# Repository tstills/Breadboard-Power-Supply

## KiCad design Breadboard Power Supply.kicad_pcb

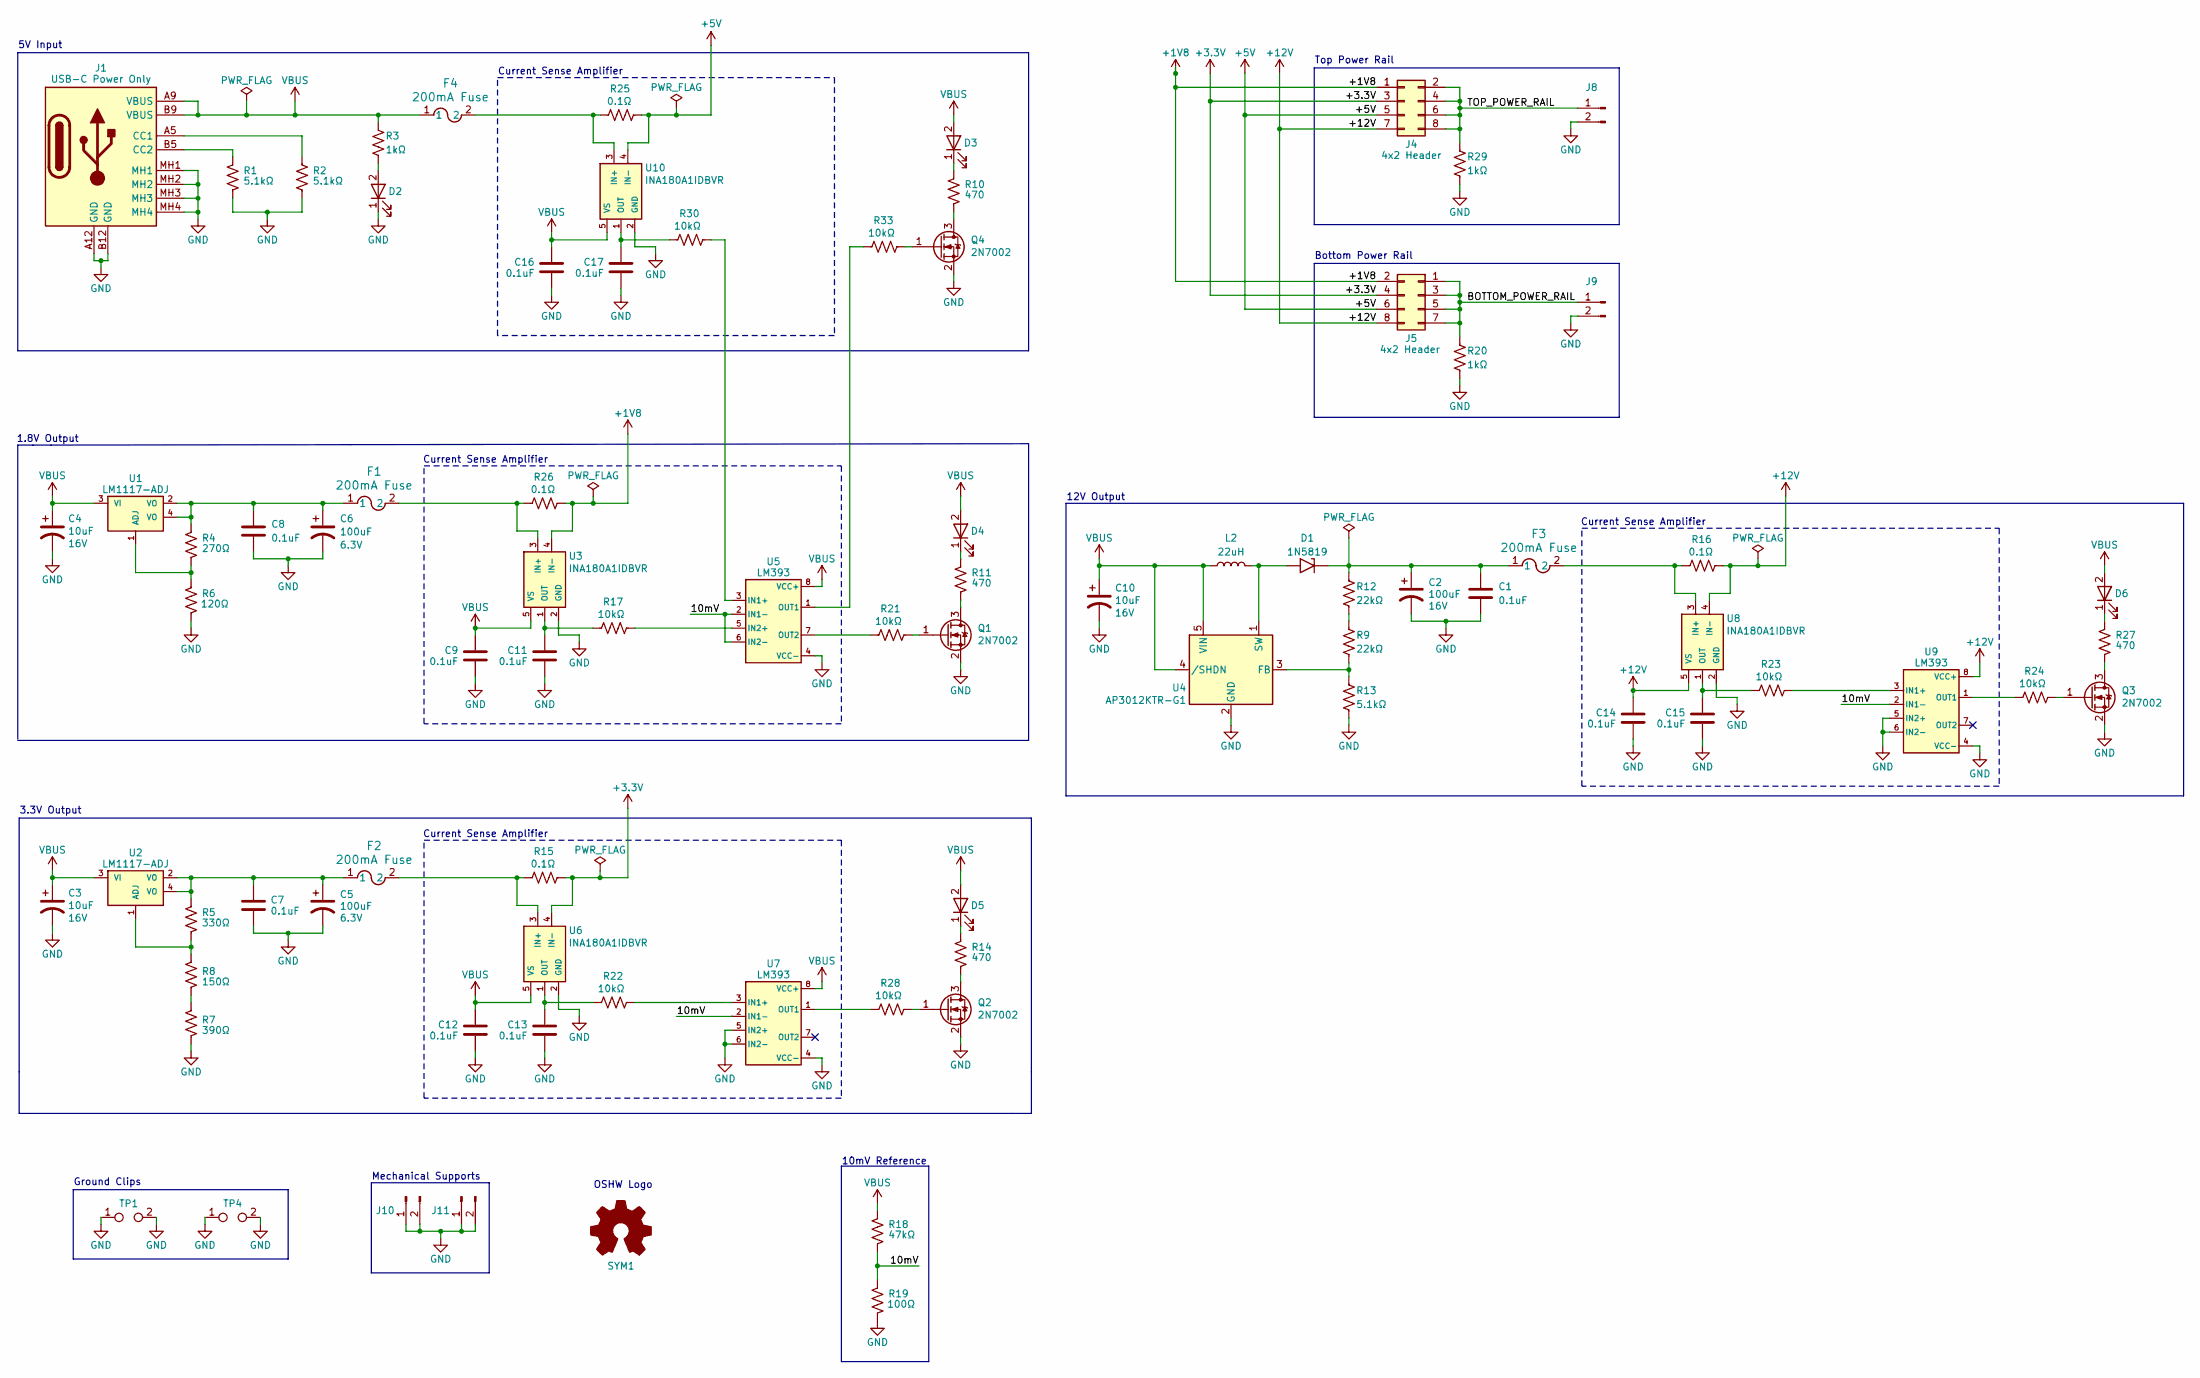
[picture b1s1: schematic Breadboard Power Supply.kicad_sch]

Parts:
C1, C7, C8, C9, C11, C12, C13, C14, C15, C16, C17: 0.1uF; C_0402_1005Metric; Digi-Key Part Num 490-14603-1-ND
C2: 100uF; 100uF 16V Capacitor; Voltage 16V; Mfg Part Num 16ZLH100MEFC5X11; Digi-Key Part Num 1189-1148-ND
C3, C4, C10: 10uF; C_0805_2012Metric; Voltage 16V; Mfg Part Num TCTP1C106M8R; Digi-Key Part Num TCTP1C106M8R
C5, C6: 100uF; 100uF 6.3V Capacitor; Voltage 6.3V; Mfg Part Num F930J107KAA; Digi-Key Part Num 478-8152-1-ND
D1: 1N5819; D_SOD-123F; Mfg Part Num 1N5819HW1-7-F; Digi-Key Part Num 1N5819HW1-7-FDICT-ND
D2, D3, D4, D5, D6: LED 0603; Mfg Part Num SML-D12U8WT86; Digi-Key Part Num 846-SML-D12U8WT86CT-ND
F1, F2, F3, F4: 200mA Fuse; Resettable Fuse 200mA; Mfg Part Num 0ZCJ0020FF2E; DigiKey Part Num 5923-0ZCJ0020FF2ECT-ND
J1: USB-C Power Only; Mfg Part Num 217175-0001; Digi-Key Part Num 900-2171750001CT-ND
J4, J5: 4x2 Header; PinHeader_2x04_P2.54mm_Vertical
J8: Conn_01x02_Male; PinHeader_1x02_P2.54mm_Vertical
J9, J10, J11: Conn_01x02_Male; PinHeader_1x02_P2.54mm_Vertical; Digi-Key Part Num 2057-PH1-02-UA-ND
L2: 22uH; L_0805_2012Metric; Mfg Part Num MLZ2012P220WT000; Digi-Key Part Num 445-15751-1-ND
Q1, Q2, Q3, Q4: 2N7002; SOT-23; Mfg Part Num 2N7002; DigiKey Part Num 4878-2N7002CT-ND
R1, R2: 5.1kΩ; R_0402_1005Metric; Digi-Key Part Num 10-ERJ-UP3F5101VCT-ND
R3, R20, R29: 1kΩ; R_0402_1005Metric; Mfg Part Num RC0603FR-07910RL; Digi-Key Part Num 311-910HRCT-ND
R4: 270Ω; R_0402_1005Metric; Digi-Key Part Num 10-ERJ-UP3F5101VCT-ND
R5: 330Ω; R_0402_1005Metric; Digi-Key Part Num 10-ERJ-UP3F5101VCT-ND
R6: 120Ω; R_0402_1005Metric; Digi-Key Part Num 10-ERJ-UP3F5101VCT-ND
R7: 390Ω; R_0402_1005Metric; Digi-Key Part Num 10-ERJ-UP3F5101VCT-ND
R8: 150Ω; R_0402_1005Metric; Digi-Key Part Num 10-ERJ-UP3F5101VCT-ND
R9, R12: 22kΩ; R_0402_1005Metric; Mfg Part Num RC0603FR-07910RL; Digi-Key Part Num 311-910HRCT-ND
R10, R11, R14, R27: 470; R_0402_1005Metric; Digi-Key Part Num 10-ERJ-UP3F5101VCT-ND
R13: 5.1kΩ; R_0402_1005Metric; Mfg Part Num RC0603FR-07910RL; Digi-Key Part Num 311-910HRCT-ND
R15, R16, R25, R26: 0.1Ω; R_0402_1005Metric; Digi-Key Part Num 10-ERJ-UP3F5101VCT-ND
R17, R21, R22, R23, R24, R28, R30, R33: 10kΩ; R_0402_1005Metric; Digi-Key Part Num 10-ERJ-UP3F5101VCT-ND
R18: 47kΩ; R_0402_1005Metric; Digi-Key Part Num 10-ERJ-UP3F5101VCT-ND
R19: 100Ω; R_0402_1005Metric; Digi-Key Part Num 10-ERJ-UP3F5101VCT-ND
SYM1: Logo_Open_Hardware_Small; OSHW-Logo_7.5x8mm_SilkScreen
TP1: TestPoint_2Pole; Keystone 1430; Digi-Key Part Num 36-1430-1-ND
TP4: TestPoint_2Pole; Keystone 1430; Digi-Key Part Num 36-1287-ND
U1: LM1117-ADJ; PARTREV O; Digi-Key Part Num 296-21114-1-ND
U2: LM1117-ADJ; Mfg Part Num TLV1117-50CDCYR; Digi-Key Part Num 296-21114-1-ND
U3, U6, U8, U10: INA180A1IDBVR; Mfg Part Num INA180A1IDBVR; Digi-Key Part Num 296-47652-1-ND
U4: AP3012KTR-G1; SOT-23-5_DIO; Mfg Part Num AP3012KTR-G1; DigiKey Part Num AP3012KTR-G1DICT-ND
U5, U7, U9: LM393; LM393 DFN8; Mfg Part Num LM393LVDSGR; Digi-Key Part Num 296-LM393LVDSGRCT-ND

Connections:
+1V8: J4.1, J5.2, R26.2, U3.4 (IN-)
+3.3V: J4.3, J5.4, R15.2, U6.4 (IN-)
+5V: J4.5, J5.6, R25.2, U10.4 (IN-)
+12V: C14.2, J4.7, J5.8, R16.2, U8.4 (IN-), U8.5 (VS), U9.8 (VCC+)
/10mV: R18.2, R19.1, U5.2 (IN1-), U5.6 (IN2-), U7.2 (IN1-), U9.2 (IN1-)
/BOTTOM_POWER_RAIL: J5.1, J5.3, J5.5, J5.7, J9.1, R20.1
/TOP_POWER_RAIL: J4.2, J4.4, J4.6, J4.8, J8.1, R29.1
GND: C1.2, C2.2, C3.2, C4.2, C5.2, C6.2, C7.2, C8.2, C9.1, C10.2, C11.1, C12.1, C13.1, C14.1, C15.1, C16.1, C17.1, D2.1, J1.A12 (GND), J1.B12 (GND), J1.MH1, J1.MH2, J1.MH3, J1.MH4, J8.2, J9.2, J10.1, J10.2, J11.1, J11.2, Q1.2 (S), Q2.2 (S), Q3.2 (S), Q4.2 (S), R1.2, R2.2, R6.2, R7.2, R13.2, R19.2, R20.2, R29.2, TP1.1, TP1.2, TP4.1, TP4.2, U3.2 (GND), U4.2 (GND), U5.4 (VCC-), U6.2 (GND), U7.4 (VCC-), U7.5 (IN2+), U7.6 (IN2-), U8.2 (GND), U9.4 (VCC-), U9.5 (IN2+), U9.6 (IN2-), U10.2 (GND)
unnamed: C5.1, C7.1, F2.1, R5.1, U2.2 (VO), U2.4 (VO)
unnamed: C6.1, C8.1, F1.1, R4.1, U1.2 (VO), U1.4 (VO)
unnamed: C1.1, C2.1, D1.1 (A1), F3.1, R12.1
unnamed: D1.2 (A2), L2.2, U4.1 (SW)
unnamed: D2.2, R3.2
unnamed: D3.1, R10.1
unnamed: D4.1, R11.1
unnamed: D5.1, R14.1
unnamed: D6.1, R27.1
unnamed: J1.A5 (CC1), R2.1
unnamed: J1.B5 (CC2), R1.1
unnamed: Q1.3 (D), R11.2
unnamed: Q1.1 (G), R21.2
unnamed: Q2.3 (D), R14.2
unnamed: Q2.1 (G), R28.2
unnamed: Q3.3 (D), R27.2
unnamed: Q3.1 (G), R24.2
unnamed: Q4.3 (D), R10.2
unnamed: Q4.1 (G), R33.2
unnamed: R7.1, R8.2
unnamed: R9.1, R12.2
unnamed: R4.2, R6.1, U1.1 (ADJ)
unnamed: R5.2, R8.1, U2.1 (ADJ)
unnamed: F1.2, R26.1, U3.3 (IN+)
unnamed: C11.2, R17.1, U3.1 (OUT)
unnamed: R9.2, R13.1, U4.3 (FB)
unnamed: R30.2, U5.3 (IN1+)
unnamed: R17.2, U5.5 (IN2+)
unnamed: R33.1, U5.1 (OUT1)
unnamed: R21.1, U5.7 (OUT2)
unnamed: F2.2, R15.1, U6.3 (IN+)
unnamed: C13.2, R22.1, U6.1 (OUT)
unnamed: R22.2, U7.3 (IN1+)
unnamed: R28.1, U7.1 (OUT1)
unnamed: F3.2, R16.1, U8.3 (IN+)
unnamed: C15.2, R23.1, U8.1 (OUT)
unnamed: R23.2, U9.3 (IN1+)
unnamed: R24.1, U9.1 (OUT1)
unnamed: F4.2, R25.1, U10.3 (IN+)
unnamed: C17.2, R30.1, U10.1 (OUT)
VBUS: C3.1, C4.1, C9.2, C10.1, C12.2, C16.2, D3.2, D4.2, D5.2, D6.2, F4.1, J1.A9 (VBUS), J1.B9 (VBUS), L2.1, R3.1, R18.1, U1.3 (VI), U2.3 (VI), U3.5 (VS), U4.4 (/SHDN), U4.5 (VIN), U5.8 (VCC+), U6.5 (VS), U7.8 (VCC+), U10.5 (VS)

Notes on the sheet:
3.3V Output
Mechanical Supports
12V Output
5V Input
Current Sense Amplifier
Top Power Rail
10mV Reference
1.8V Output
OSHW Logo
Ground Clips
Bottom Power Rail

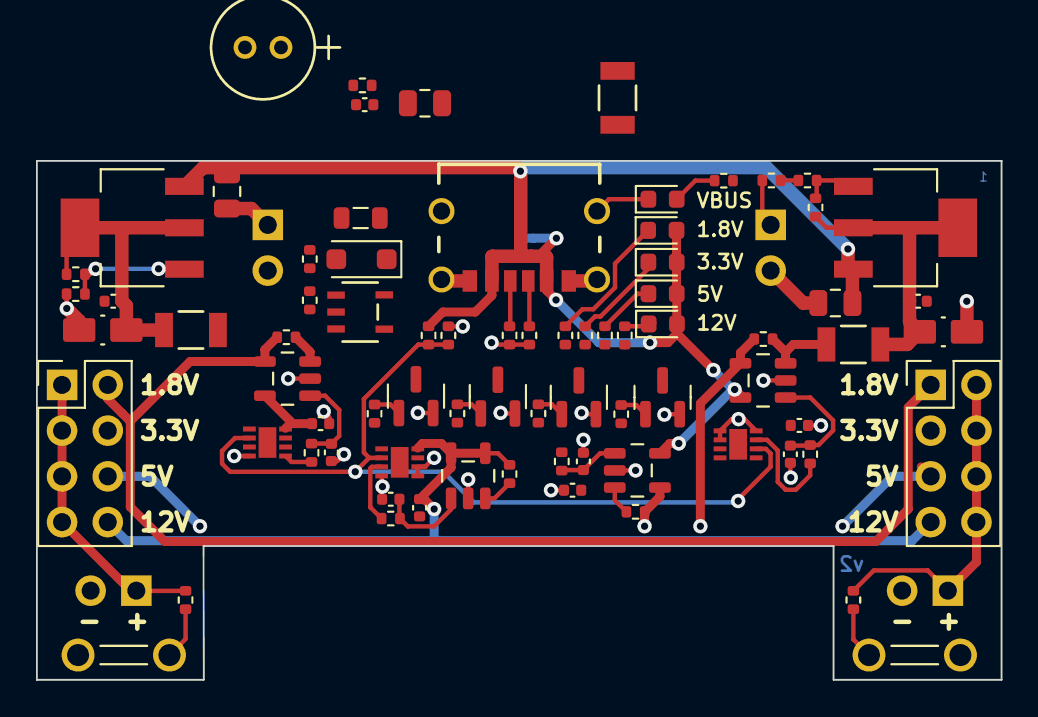
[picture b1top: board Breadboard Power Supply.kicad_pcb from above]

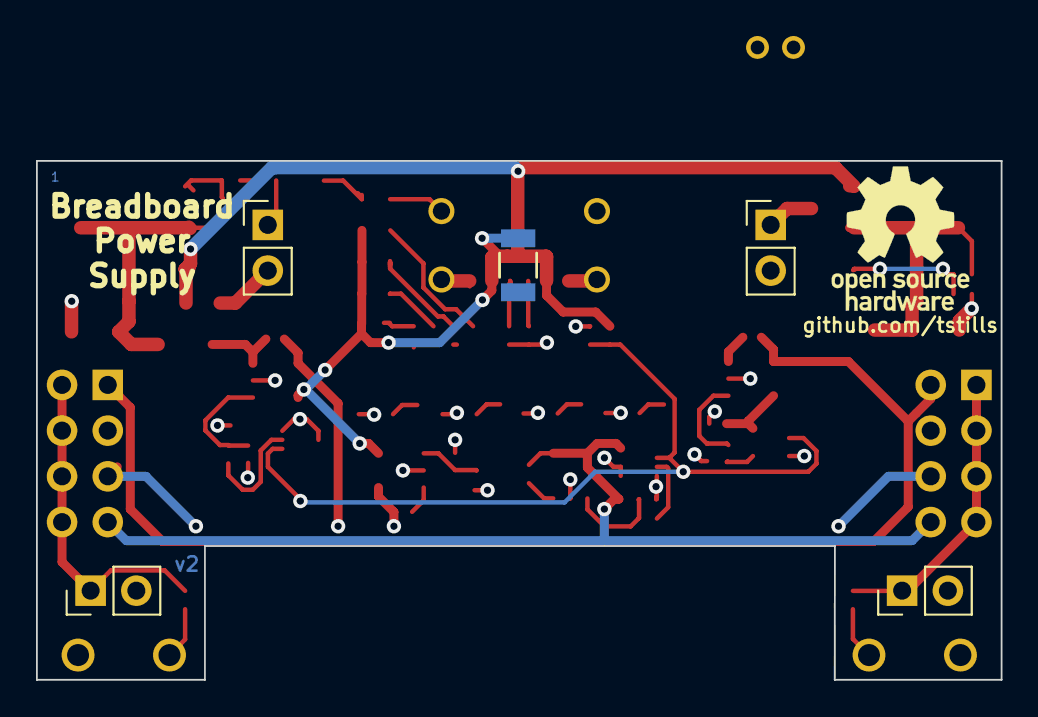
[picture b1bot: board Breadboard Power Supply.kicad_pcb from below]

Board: 4 copper layers, 53.6 x 28.8 mm, 83 parts (6 on the bottom side), 49 nets.

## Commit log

2023-01-28 Redrew schematic with 1.8V and 3.3V linear regulators.
2023-02-02 Completed routing with no DRCs.
2023-02-03 Refined the layout.
2023-02-03 Initial checkin of Gerbers.
2023-02-03 Refined board layout.
2023-02-06 Initial library checkin.
2023-02-06 Deleted unneeded files.
2023-02-06 Added ground clips.
2023-02-06 Tweaked the silkscreen.
2023-02-09 Generated Gerbers.
2023-02-09 Added board dimensions.
2023-02-09 Completed BOM.
2023-02-09 Finished BOM.
2023-02-10 Finished BOM and ordered parts.
2023-02-12 Replaced fixed voltage LM1117's with the adjustable versions.
2023-02-19 Update.
2023-02-19 Snapped stuff to grid.
2023-02-19 Updates.
2023-02-19 Breadboard Mechanicals.vsdx initial checkin.
2023-02-19 5V wasn't hooked up correctly.
2023-02-19 The power rails were mixed up.
2023-02-19 Fixed an issue where the power rails were mixed up.
2023-02-19 Changed LM1117 symbol.
2023-02-20 Changed USB connector from through hole to surface mount.
2023-02-20 Finished place and route.
2023-02-20 Updated some part numbers.
2023-02-20 Backed up the voltage regulators to what was in v1.
2023-02-20 Got schematic on grid.
2023-02-21 Layout tweaks.
2023-02-25 Release Candidate.
2023-02-25 Updated User Drawings layer.
2023-02-25 Got rid of some unneeded local libraries.
2023-02-25 Got rid of local libraries.
2023-02-25 Put global libraries under version control.
2023-02-26 Version 2.
2023-02-27 Got rid of an extra file.
2023-03-14 Updated To Do list from board evaluation.
2023-03-14 Replaced individual voltage headers with 02x03 header.
2023-03-14 Updated the version number.
2023-03-14 Swapped power and ground rails.
2023-03-14 Added USB-C 3D model.
2023-03-14 Fixed DRC errors.
2023-03-15 Preliminary place and route.
2023-03-16 Changed LED to an 0603 footprint.
2023-03-16 Updated the To Do list.
2023-03-17 Fixed some DRCs.
2023-03-20 Created v3 Gerbers.
2023-04-11 Finished layout.
2023-04-12 Minor tweaks.
2023-04-12 Moved mechanical support closer together to make room for the back side silkscreen.
2023-04-14 v4 release candidate.
2023-04-14 Updates to User Drawings layer.
2023-04-22 Made the board 0.01 wider on each side.
2023-04-22 Cleaned up the schematic.
2023-04-23 Completed layout.
2023-04-23 Replaced 10uF footprints with 0805.
2023-04-23 Added an 0402 resistor.
2023-04-23 Created Gerbers
2023-04-27 Added feedback.
2023-05-01 Implemented most items in Feedback.
2023-05-01 Attached a Zener diode to VBUS.
2023-05-01 Fixed ERC issues.
2023-05-06 Made the mounting holes on the USB-C connector 20% smaller.
2023-05-07 Added 3D model for the Zener diode.
2023-05-08 Added OSHW logo.
2023-05-08 Got rid of top level Zener diode.
2023-05-08 Resized board.
2023-05-08 Filled out global part number fields
2023-05-08 Updated the BOM
2023-05-08 Fixed some formatting.
2023-05-08 Replaced the Zener diode's footprint with one in the default library.
2023-05-08 Moved the USB-C symbol to the local directory.
2023-05-08 Placed LEDs near voltage regulators.
2023-05-08 Added a symbol for the OSHW logo.
2023-05-09 Moved the USB-C to the local footprints library.
2023-05-09 Added some copper fills to the PCB.
2023-05-14 Created Gerbers.
2023-05-14 Updated BOM.
2023-05-19 Version 7
2023-05-25 Moved traces and fills away from board edges.
2023-05-25 Made the font for github.com/tstills larger.
2023-05-25 Made the USB mounting holes 10% smaller.
2023-05-25 Moved some caps around.
2023-05-25 Made some edits to the USB footprint.
2023-05-25 Went from two LEDs to a single one powered by 5V.
2023-05-25 Generated Gerber fiels.
2023-06-06 Updated resistor value.
2023-06-06 Adjusted resistor value.
2023-06-08 Changed resistor to 680 ohms.
2023-06-08 Flipped the headers going to the power rails.
2023-06-08 Updated the resistor to 1k.
2023-06-08 Updated the version number to v9.
2023-06-08 Generated Gerber files.
2023-06-08 Compressed Gerber files.
2023-06-14 Made the font on the URL thicker.
2023-06-21 Deleted local symbols.
2023-06-21 Moved local footprints to the global library.
2023-06-21 Updated schematic to have variable regulators.
2023-06-22 Updated version numbers.
2023-06-28 Got rid of the Zener diode.
2023-06-28 Changed voltage regulator symbol.
2023-06-28 Cleaned up the fill zones.
2023-06-28 Moved some vias that were poking through the back side silkscreen.
2023-06-28 Put back in some 3D models.
2023-06-28 Added some comments.
2023-06-29 Tweaked the mechanical supports.
2023-06-29 Updated the User Drawings.
2023-07-10 Updated potentiometer part number.
2023-07-15 Got rid of To Do list.
2023-07-15 Redid schematic with both fixed and adjustable voltage regulators.
2023-07-15 Feature complete schematic.
2023-08-01 Feedback from first prototype.
2023-12-21 Moved the to do list to ReMarkable.
2023-12-22 Fixed stuff on To Do list.
2023-12-23 Changed the version number from 0.12 to 1.12.
2024-01-08 Drew schematic for 12V regulstor.
2024-01-09 Changed the voltage regulator for 12V.
2024-01-21 Make the OSHW logo larger.
2024-01-22 Changed capacitor footprints from 1210 to 0805.
2024-01-22 Moved some passives from the back to the front.
2024-01-22 Added a copper fill for the switcher.
2024-01-22 The voltage selection headers were slightly off.
2024-01-22 Lined up silkscreen + and -.
2024-01-22 Moved more passives to the front side.
2024-01-31 Hid D2 reference designator.
2024-01-31 Tweak
2024-02-01 1.8V wasn't connected on the left and right sides.
2024-02-01 Nudged the power rail supports over 0.04
2024-02-10 Moved the plus and minus silkscreen to align with the mounting holes.
2024-02-10 Silkscreen tweaks.
2024-02-10 The Zener diode was D1 on the schematic and D2 on the PCB.
2024-02-17 Added 3D models for the ground clips.
2024-02-20 Changed to global LED footprint.
2024-02-20 Updated Schottky Diode.
2024-03-27 Adjusted width of power rail supports.
2024-03-28 Released v1.16.
2024-03-29 Changed to global version of LED 0603.
2024-07-31 v1.0
2024-08-11 Generated Gerbers
2024-09-15 Got ready for public release.
2025-08-25 Generated Gerber files
